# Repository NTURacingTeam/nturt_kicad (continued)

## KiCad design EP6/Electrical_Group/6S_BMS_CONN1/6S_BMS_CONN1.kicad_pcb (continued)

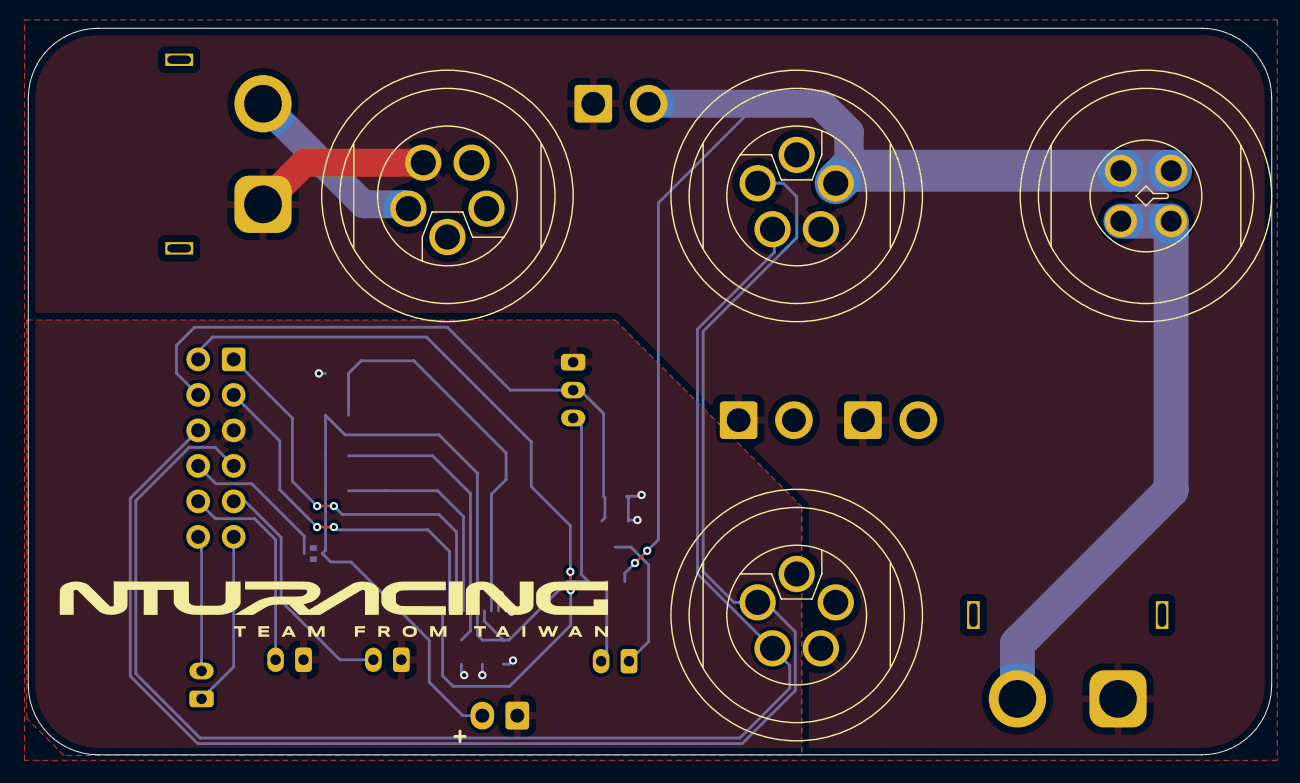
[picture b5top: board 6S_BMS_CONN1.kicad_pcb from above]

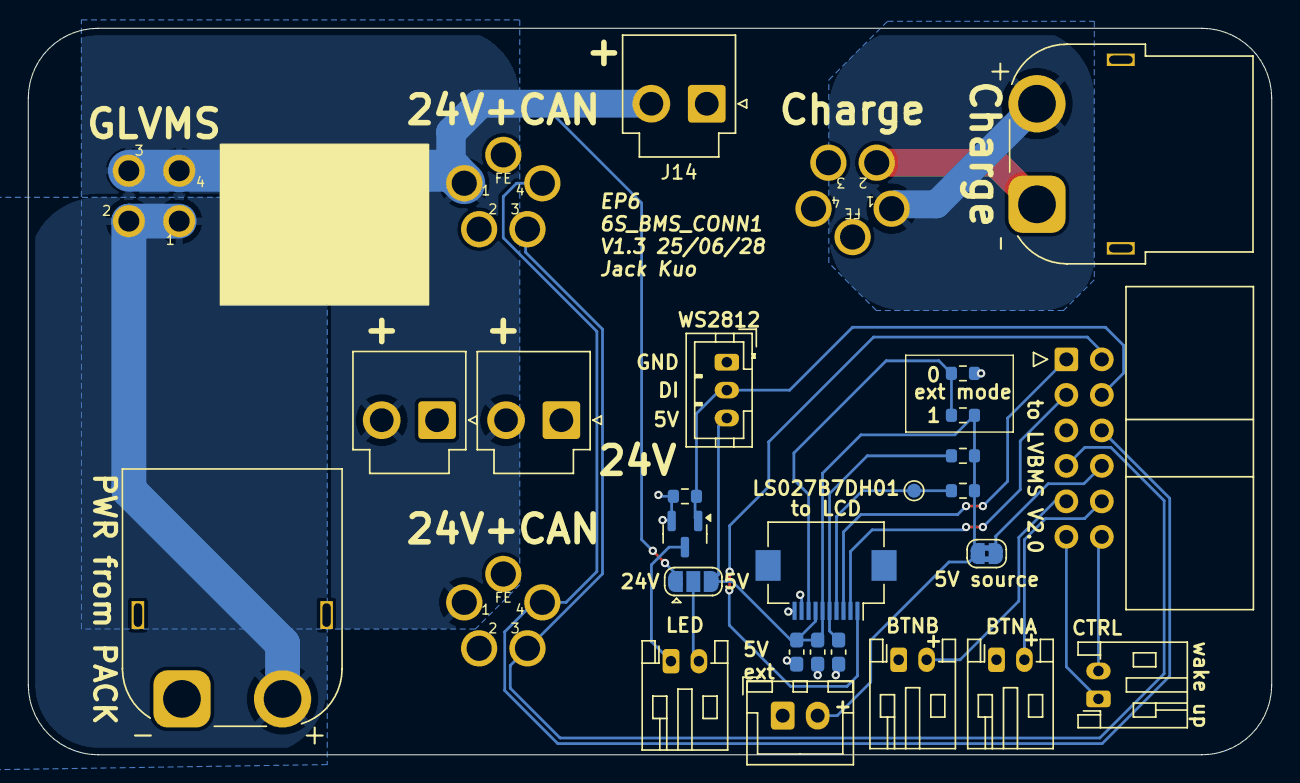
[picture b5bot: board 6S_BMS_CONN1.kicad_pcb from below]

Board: 2 copper layers, 89.0 x 52.0 mm, 29 parts (25 on the bottom side), 22 nets.
